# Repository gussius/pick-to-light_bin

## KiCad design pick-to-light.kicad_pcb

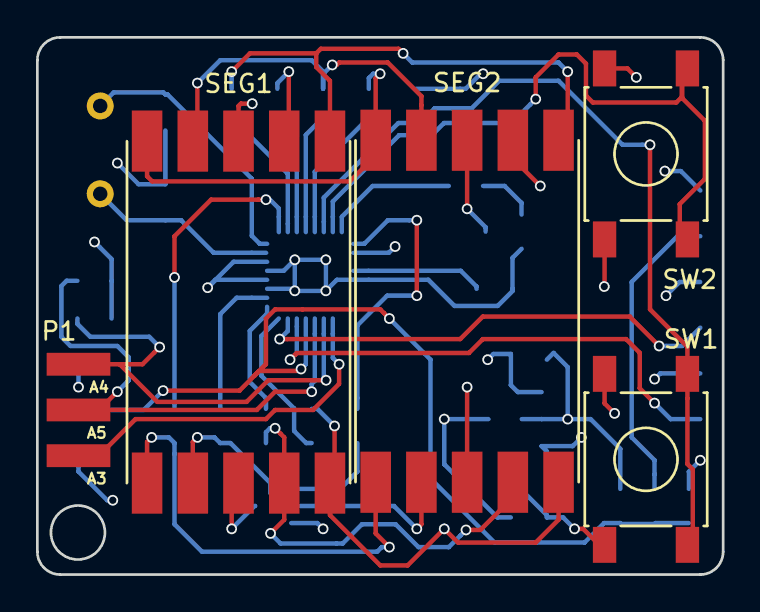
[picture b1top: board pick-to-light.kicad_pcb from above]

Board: 4 copper layers, 38.1 x 29.8 mm, 34 parts (0 on the bottom side), 37 nets.

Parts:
C2, C5: 0.1uF; C_0805
C3: 10uF; C_0805
C4: 22uF; C_0805
C6: 0.1uF; C_0805_HandSoldering
C7, C8: 15pF; C_0805
IC1: ATMEGA168PA-A; QFN-32-1EP_5x5mm_Pitch0.5mm
P1: 2x3-male-pin-header-smd-board-edge
P2: CONN_02X03; prog_smd_pads
Q1, Q2: BC849; SOT-23
R1, R2, R3, R4, R5, R6, R7, R8: 110; R_0805
R9, R12: 4K7; R_0805
R10, R11, R15: 10k; R_0805
R13, R14: 22k; R_0805
R16: 0; C_0603_HandSoldering
SEG1, SEG2: HDSP-C5A3; ACSC56-41SRWA-F01
SW1, SW2: SW_PUSH; SW_SPST_PTS645
U1: LD1117S33TR; SOT89-3_Housing
Y1: Crystal; Crystal_HC49-U_Vertical

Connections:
A3: IC1.26, P1.5
A4: IC1.27, P1.1, R13.2
A5: IC1.28, P1.3, R14.2
GND: C2.2, C3.2, C4.2, C5.2, C7.2, C8.2, IC1.3, IC1.5, IC1.21, P1.6, P2.1, P2.3, Q1.2, Q2.2, R16.1, SW1.2, SW2.2, U1.1
unnamed: C2.1, IC1.20
unnamed: C6.2, P2.2
unnamed: IC1.1, R7.2
unnamed: IC1.2, R6.2
unnamed: IC1.9, R5.2
unnamed: IC1.10, R4.2
unnamed: IC1.11, R3.2
unnamed: IC1.12, R2.2
unnamed: IC1.13, R1.2
unnamed: IC1.14, R11.1, SW1.1
unnamed: IC1.15, R10.1, SW2.1
unnamed: IC1.16, R12.2
unnamed: IC1.17, R9.2
unnamed: IC1.32, R8.2
unnamed: Q1.1, R9.1
unnamed: Q1.3, SEG1.3, SEG1.8
unnamed: Q2.1, R12.1
unnamed: Q2.3, SEG2.3, SEG2.8
unnamed: R1.1, SEG1.10, SEG2.10
unnamed: R2.1, SEG1.9, SEG2.9
unnamed: R3.1, SEG1.7, SEG2.7
unnamed: R4.1, SEG1.6, SEG2.6
unnamed: R5.1, SEG1.1, SEG2.1
unnamed: R6.1, SEG1.2, SEG2.2
unnamed: R7.1, SEG1.4, SEG2.4
unnamed: R8.1, SEG1.5, SEG2.5
RAW: C3.1, P1.2, U1.3
RESET: C6.1, IC1.29, P1.4, R15.2, R16.2
RX1: IC1.30, P2.6
TX0: IC1.31, P2.4
VCC: C4.1, C5.1, IC1.4, IC1.6, IC1.18, P2.5, R10.2, R11.2, R13.1, R14.1, R15.1, U1.2
XTAL1: C7.1, IC1.7, Y1.1
XTAL2: C8.1, IC1.8, Y1.2

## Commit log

2015-12-13 replaced chip package to QFN-32
2016-01-18 Sent out for prototyping
